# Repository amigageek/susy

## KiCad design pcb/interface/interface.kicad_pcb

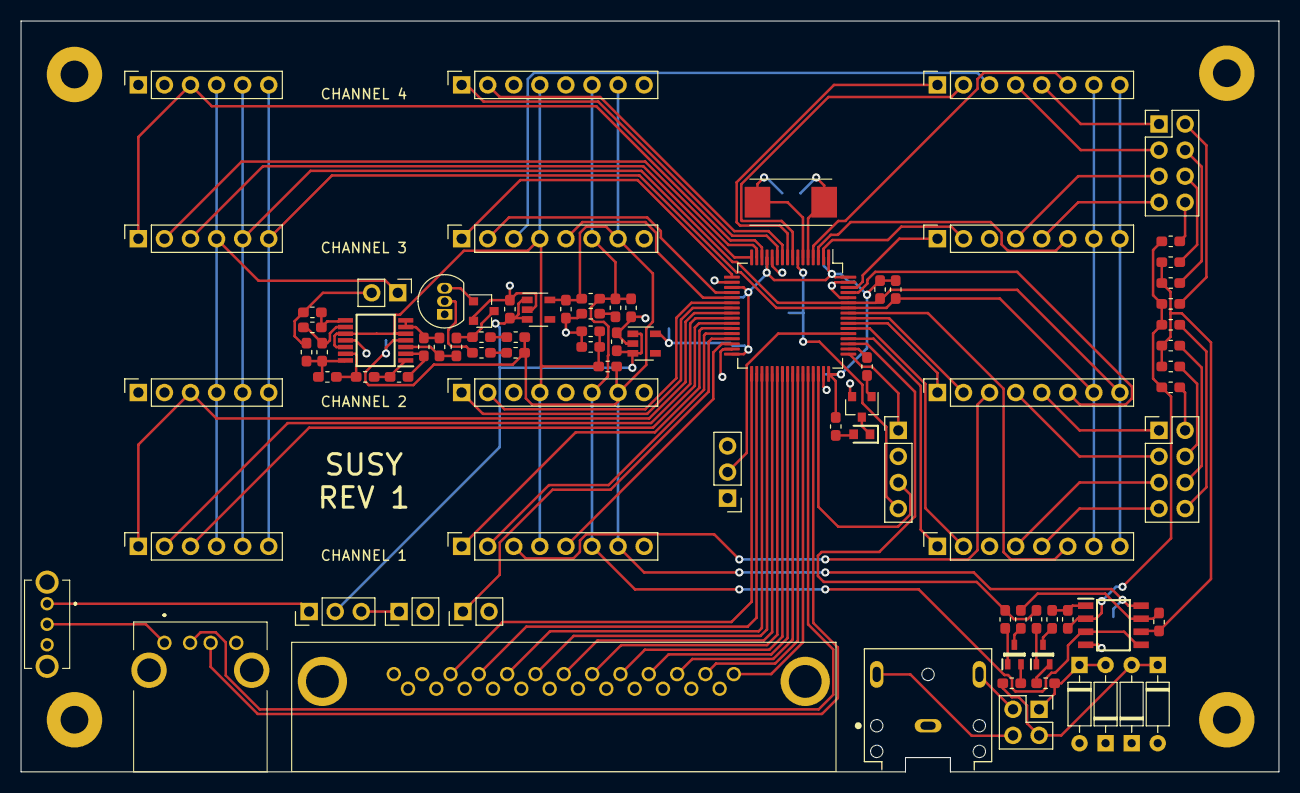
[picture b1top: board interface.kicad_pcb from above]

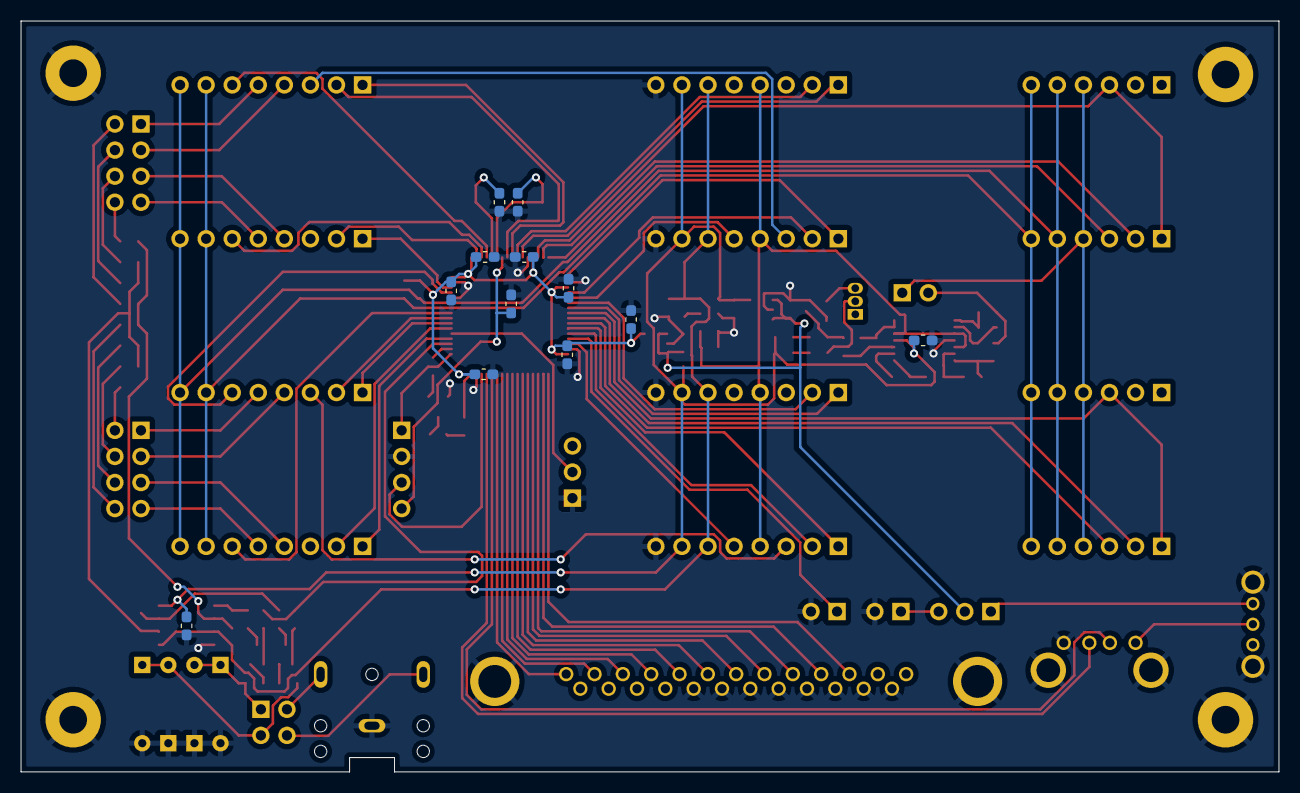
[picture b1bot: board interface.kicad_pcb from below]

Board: 2 copper layers, 122.6 x 73.2 mm, 101 parts (12 on the bottom side), 112 nets.

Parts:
C1, C2, C3, C4, C5, C6, C16, C19, C20: 100nF; C_0603_1608Metric_Pad1.05x0.95mm_HandSolder
C7: 10nF; C_0603_1608Metric_Pad1.05x0.95mm_HandSolder
C8, C10, C14, C15, C17, C18: 1uF; C_0603_1608Metric_Pad1.05x0.95mm_HandSolder
C9, C11: 4.7uF; C_0603_1608Metric_Pad1.05x0.95mm_HandSolder
C12, C13: 8pF; C_0603_1608Metric_Pad1.05x0.95mm_HandSolder
D1, D2, D3, D4: 1N4148; D_DO-35_SOD27_P7.62mm_Horizontal
H1, H2, H3, H4: MountingHole_Pad; MountingHole_2.7mm_M2.5_Pad
IC1: MCP6072-E_SN; SOIC127P600X175-8N
IC2: MCP6074-E_ST; SOP65P640X120-14N
J1, J2, J3, J4: Conn_01x06_Female; PinSocket_1x06_P2.54mm_Vertical
J5, J6, J7, J8, J9, J10, J11, J12: Conn_01x08_Female; PinSocket_1x08_P2.54mm_Vertical
J13: Conn_01x04_Male; PinHeader_1x04_P2.54mm_Vertical
J14: Parallel/USB; PinHeader_1x03_P2.54mm_Vertical
J15: D25S33E4PA00LF
J16: UJ2-AH-4-TH; UJ2AH4TH
J17: Spare; PinHeader_1x02_P2.54mm_Vertical
J18: Pwr Sel; PinHeader_1x03_P2.54mm_Vertical
J19: Pwr Ext; PinHeader_1x02_P2.54mm_Vertical
J20: SJ1-3523N; CUI_SJ1-3523N
J21: Conn_01x02_Male; PinHeader_1x02_P2.54mm_Vertical
J22: Conn_02x02_Top_Bottom; PinHeader_2x02_P2.54mm_Vertical
J23, J24: Conn_02x04_Top_Bottom; PinHeader_2x04_P2.54mm_Vertical
LED1: SML-D12U1WT86; LEDC1608X65N
Q1, Q4: MMBT3904; SOT-23
Q2, Q3: NX3008NBKW,115; SOT65P210X110-3N
R1, R2: 10k; R_0603_1608Metric_Pad1.05x0.95mm_HandSolder
R3: 47; R_0603_1608Metric_Pad1.05x0.95mm_HandSolder
R4: 33K; R_0603_1608Metric_Pad1.05x0.95mm_HandSolder
R5, R6, R7, R8, R9, R10, R12, R14, R15, R16, R17, R19, R20, R21, R22, R30, R32: 100k; R_0603_1608Metric_Pad1.05x0.95mm_HandSolder
R11, R13: 1k; R_0603_1608Metric_Pad1.05x0.95mm_HandSolder
R18, R23: 300k; R_0603_1608Metric_Pad1.05x0.95mm_HandSolder
R24, R25, R26, R27, R29, R33, R34: 1; R_0603_1608Metric_Pad1.05x0.95mm_HandSolder
R28, R31: 2k; R_0603_1608Metric_Pad1.05x0.95mm_HandSolder
R35, R36: 0; R_0603_1608Metric_Pad1.05x0.95mm_HandSolder
S1: OS102011MA1QN1C
U1: STM32F070RBTx; LQFP-64_10x10mm_P0.5mm
U2, U3: MIC5365-3.3YD5; SOT-23-5
U4: LM385BZ-1.2; TO-92_Inline
Y1: NX8045GB-8.000M-STD-CSJ-1; NX8045GB8000MSTDCSJ1

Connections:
/Line Driver (L)/LINE_OUT: D1.2, D2.1, J22.1, R11.1
/Line Driver (R)/LINE_OUT: D3.2, D4.1, J22.2, R13.1
/Mixer (L)/IN1: J24.8, R14.2
/Mixer (L)/IN2: J24.2, R15.2
/Mixer (L)/IN3: J23.8, R16.2
/Mixer (L)/IN4: J23.2, R17.2
/Mixer (L)/OP-: IC1.2, R14.1, R15.1, R16.1, R17.1, R18.2
/Mixer (R)/IN1: J24.6, R19.2
/Mixer (R)/IN2: J24.4, R20.2
/Mixer (R)/IN3: J23.6, R21.2
/Mixer (R)/IN4: J23.4, R22.2
/Mixer (R)/OP-: IC1.6, R19.1, R20.1, R21.1, R22.1, R23.2
/Noise/OUT: J21.2, R35.1, R36.1
/Regulator (VCC)/VIN: C8.1, C10.1, J18.2, U2.1, U2.3, U3.1, U3.3
FSEL1A: J9.2, U1.54
FSEL1B: J9.1, U1.52
FSEL2A: J10.2, U1.56
FSEL2B: J10.1, U1.55
FSEL3A: J11.2, U1.2
FSEL3B: J11.1, U1.62
FSEL4A: J12.2, U1.8
FSEL4B: J12.1, U1.9
GATE1: J9.6, U1.57
GATE2: J10.6, U1.61
GATE3: J11.6, U1.3
GATE4: J12.6, U1.4
GND: C1.2, C2.1, C3.1, C4.1, C5.1, C6.1, C7.1, C8.2, C9.2, C10.2, C11.2, C12.1, C13.1, C14.2, C15.2, C16.2, C20.2, D1.1, D2.2, D3.1, D4.2, H1.1, H2.1, H3.1, H4.1, IC1.4, IC2.11, J5.8, J6.8, J7.8, J8.8, J13.2, J14.1, J15.2, J15.4, J15.6, J15.8, J15.10, J15.12, J15.14, J15.16, J15.MH1, J15.MH2, J16.4, J16.MH1, J16.MH2, J17.2, J19.2, J20.1, Q1.2, Q4.2, R6.2, R9.2, S1.MH1, S1.MH2, U1.12, U1.18, U1.31, U1.47, U1.60, U1.63, U2.2, U3.2
LEFT: C17.2, IC1.1, R18.1
LEFT1: J9.5, J24.7
LEFT2: J10.5, J24.1
LEFT3: J11.5, J23.7
LEFT4: J12.5, J23.1
LINEL: J20.2, J22.3
LINER: J20.3, J22.4
LINE_EN: R10.1, R12.1, U1.51
NOISE: J1.4, J2.4, J3.4, J4.4, J21.1
unnamed: C1.1, J13.4, U1.7
unnamed: C12.2, U1.6, Y1.2
unnamed: C13.2, U1.5, Y1.1
unnamed: C17.1, Q2.3
unnamed: C18.1, Q3.3
unnamed: C19.1, IC2.3, R29.1
unnamed: C19.2, Q4.3, R27.2
unnamed: IC2.1, R30.1, R31.2
unnamed: IC2.2, R28.2, R30.2
unnamed: IC2.8, R33.2, R36.2
unnamed: IC2.9, R33.1, R34.2
unnamed: IC2.13, R31.1, R32.2
unnamed: IC2.14, R32.1, R34.1, R35.2
unnamed: J5.3, J10.3
unnamed: J7.3, J12.3
unnamed: J13.1, U1.49
unnamed: J13.3, U1.46
unnamed: J14.2, U1.53
unnamed: J16.1, S1.2
unnamed: J17.1, U1.29
unnamed: J18.3, J19.1
unnamed: LED1.1, Q1.3
unnamed: LED1.2, R3.2
unnamed: Q1.1, R4.2
unnamed: Q2.1, R10.2
unnamed: Q2.2, R11.2
unnamed: Q3.1, R12.2
unnamed: Q3.2, R13.2
unnamed: Q4.1, U4.3
unnamed: R4.1, U1.50
unnamed: R8.2, R9.1
unnamed: R24.2, R25.1
unnamed: R25.2, U4.2
unnamed: R26.2, R27.1
OSEL1A: J5.2, U1.28
OSEL1B: J5.1, U1.27
OSEL2A: J6.2, U1.22
OSEL2B: J6.1, U1.23
OSEL3A: J7.2, U1.20
OSEL3B: J7.1, U1.17
OSEL4A: J8.2, U1.10
OSEL4B: J8.1, U1.11
PACK: J15.7, U1.34
PBUSY: J15.5, U1.33
PDATA0: J15.23, U1.42
PDATA1: J15.21, U1.41
PDATA2: J15.19, U1.40
PDATA3: J15.17, U1.39
PDATA4: J15.15, U1.38
PDATA5: J15.13, U1.37
PDATA6: J15.11, U1.36
PDATA7: J15.9, U1.35
PSTROBE: J15.25, U1.43
RIGHT: C18.2, IC1.7, R23.1
RIGHT1: J9.4, J24.5
RIGHT2: J10.4, J24.3
RIGHT3: J11.4, J23.5
RIGHT4: J12.4, J23.3
RMSEL1: J5.5, U1.30
RMSEL2: J7.5, U1.21
SCL: J1.6, J2.6, J3.6, J4.6, J9.7, J10.7, J11.7, J12.7, R1.2, U1.58
SDA: J1.5, J2.5, J3.5, J4.5, J9.8, J10.8, J11.8, J12.8, R2.2, U1.59
SYNC_DIS1: J1.2, U1.25
SYNC_DIS2: J3.2, U1.15
SYNC_OUT1: J1.3, U1.26
SYNC_OUT2: J1.1, J2.3, U1.24
SYNC_OUT3: J3.3, U1.16
SYNC_OUT4: J3.1, J4.3, U1.14
UDATA+: J16.3, U1.45
UDATA-: J16.2, U1.44
VBUS: J18.1, S1.1
VCC: C9.1, C16.1, C20.1, IC1.8, IC2.4, J5.7, J6.7, J7.7, J8.7, R5.1, R7.1, R24.1, R26.1, U2.5
VDD: C2.2, C3.2, C4.2, C5.2, C6.2, C7.2, C11.1, R1.1, R2.1, R3.1, U1.1, U1.13, U1.19, U1.32, U1.48, U1.64, U3.5
VGND_REF: C15.1, IC1.3, IC1.5, J5.6, J6.6, J7.6, J8.6, R7.2, R8.1
VHALF: IC2.6, IC2.7, R28.1, R29.2
VHALF_REF: C14.1, IC2.5, IC2.10, IC2.12, J5.4, J6.4, J7.4, J8.4, R5.2, R6.1

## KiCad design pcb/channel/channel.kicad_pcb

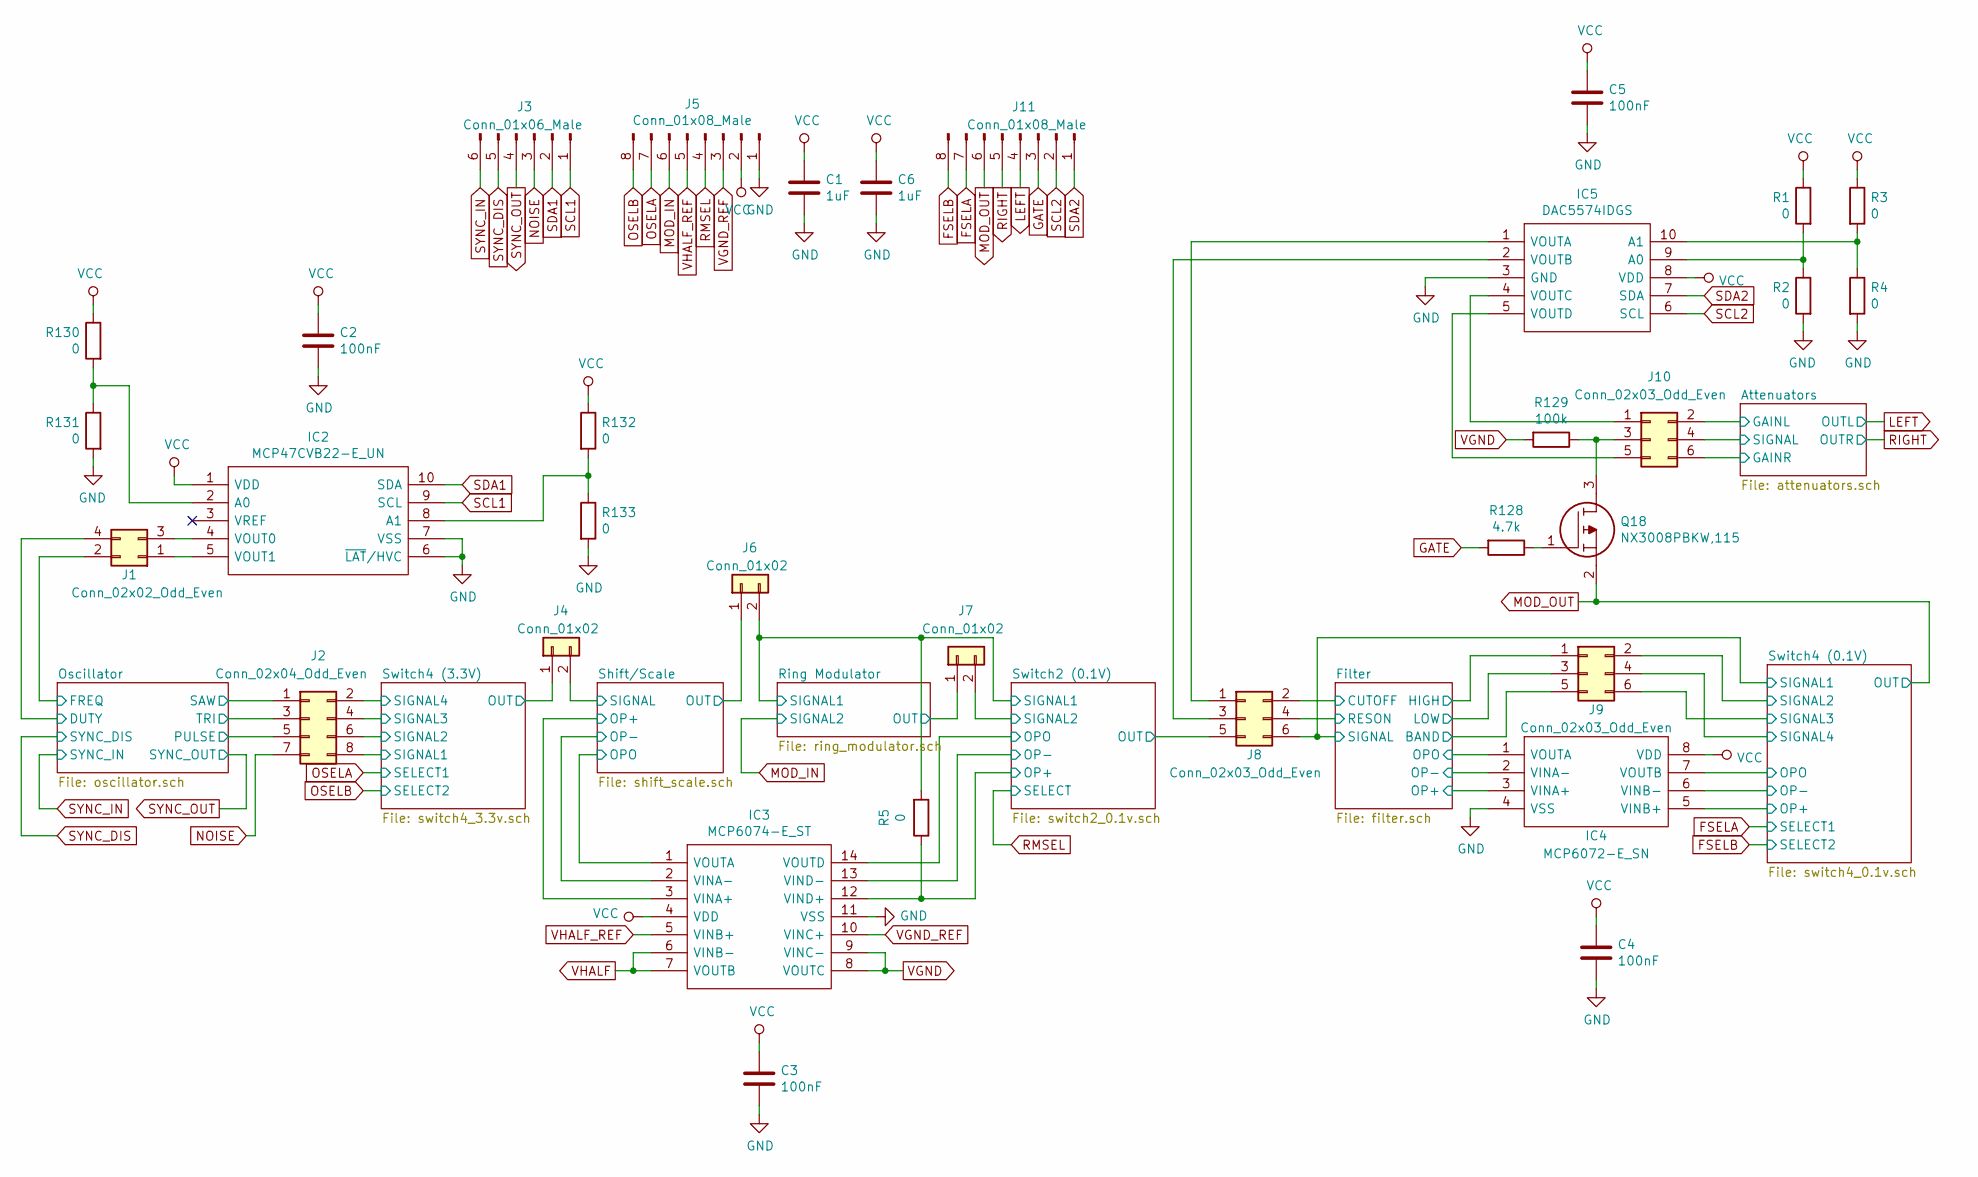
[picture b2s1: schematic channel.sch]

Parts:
C1, C6: 1uF; C_0603_1608Metric_Pad1.08x0.95mm_HandSolder
C2, C3, C4, C5: 100nF; C_0603_1608Metric_Pad1.08x0.95mm_HandSolder
IC2: MCP47CVB22-E_UN; SOP50P490X110-10N; Manufacturer_Part_Number MCP47CVB22-E/UN; Mouser Part Number 579-MCP47CVB22-E/UN
IC3: MCP6074-E_ST; SOP65P640X120-14N; Manufacturer_Part_Number MCP6074-E/ST; Mouser Part Number 579-MCP6074-E/ST
IC4: MCP6072-E_SN; SOIC127P600X175-8N; Manufacturer_Part_Number MCP6072-E/SN; Mouser Part Number 579-MCP6072-E/SN
IC5: DAC5574IDGS; SOP50P490X110-10N; Manufacturer_Part_Number DAC5574IDGS; Mouser Part Number 595-DAC5574IDGS
J1: Conn_02x02_Odd_Even; PinHeader_2x02_P2.54mm_Vertical
J2: Conn_02x04_Odd_Even; PinHeader_2x04_P2.54mm_Vertical
J3: Conn_01x06_Male; PinHeader_1x06_P2.54mm_Horizontal
J4, J6, J7: Conn_01x02; PinHeader_1x02_P2.54mm_Vertical
J5, J11: Conn_01x08_Male; PinHeader_1x08_P2.54mm_Horizontal
J8, J9, J10: Conn_02x03_Odd_Even; PinHeader_2x03_P2.54mm_Vertical
Q18: NX3008PBKW,115; SOT65P210X110-3N; Manufacturer_Part_Number NX3008PBKW,115; Mouser Part Number 771-NX3008PBKW,115
R1, R2, R3, R4, R5, R130, R131, R132, R133: 0; R_0603_1608Metric_Pad1.05x0.95mm_HandSolder
R128: 4.7k; R_0603_1608Metric_Pad1.05x0.95mm_HandSolder
R129: 100k; R_0603_1608Metric_Pad1.05x0.95mm_HandSolder

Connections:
/Attenuators/GAINL: J10.2; also elsewhere on the board
/Attenuators/GAINR: J10.6; also elsewhere on the board
/Attenuators/SIGNAL: J10.4; also elsewhere on the board
/Filter/BAND: J9.5; also elsewhere on the board
/Filter/CUTOFF: J8.2; also elsewhere on the board
/Filter/HIGH: J9.1; also elsewhere on the board
/Filter/LOW: J9.3; also elsewhere on the board
/Filter/OP+: IC4.3 (VINA+); also elsewhere on the board
/Filter/OP-: IC4.2 (VINA-); also elsewhere on the board
/Filter/OPO: IC4.1 (VOUTA); also elsewhere on the board
/Filter/RESON: J8.4; also elsewhere on the board
/Filter/SIGNAL: J8.6; also elsewhere on the board
/Oscillator/DUTY: J1.4; also elsewhere on the board
/Oscillator/FREQ: J1.2; also elsewhere on the board
/Oscillator/PULSE: J2.5; also elsewhere on the board
/Oscillator/SAW: J2.1; also elsewhere on the board
/Oscillator/TRI: J2.3; also elsewhere on the board
/Ring Modulator/OUT: J7.1; also elsewhere on the board
/Ring Modulator/SIGNAL1: J6.2, R5.2; also elsewhere on the board
/Shift/Scale/OP+: IC3.3 (VINA+); also elsewhere on the board
/Shift/Scale/OP-: IC3.2 (VINA-); also elsewhere on the board
/Shift/Scale/OPO: IC3.1 (VOUTA), J6.1; also elsewhere on the board
/Shift/Scale/SIGNAL: J4.2; also elsewhere on the board
/Switch2 (0.1V)/OP+: IC3.12 (VIND+), R5.1; also elsewhere on the board
/Switch2 (0.1V)/OP-: IC3.13 (VIND-), IC3.14 (VOUTD), J8.5
/Switch2 (0.1V)/SIGNAL2: J7.2; also elsewhere on the board
/Switch4 (0.1V)/OP+: IC4.5 (VINB+); also elsewhere on the board
/Switch4 (0.1V)/SIGNAL2: J9.2; also elsewhere on the board
/Switch4 (0.1V)/SIGNAL3: J9.6; also elsewhere on the board
/Switch4 (0.1V)/SIGNAL4: J9.4; also elsewhere on the board
/Switch4 (3.3V)/OUT: J4.1; also elsewhere on the board
/Switch4 (3.3V)/SIGNAL1: J2.8; also elsewhere on the board
/Switch4 (3.3V)/SIGNAL2: J2.6; also elsewhere on the board
/Switch4 (3.3V)/SIGNAL3: J2.4; also elsewhere on the board
/Switch4 (3.3V)/SIGNAL4: J2.2; also elsewhere on the board
FSELA: J11.7; also elsewhere on the board
FSELB: J11.8; also elsewhere on the board
GATE: J11.3, R128.2
GND: C1.2, C2.2, C3.2, C4.2, C5.2, C6.2, IC2.6 (~LAT~/HVC), IC2.7 (VSS), IC3.11 (VSS), IC4.4 (VSS), IC5.3 (GND), J5.1, R2.2, R4.2, R131.2, R133.2; also elsewhere on the board
LEFT: J11.4; also elsewhere on the board
MOD_IN: J5.6; also elsewhere on the board
MOD_OUT: IC4.6 (VINB-), IC4.7 (VOUTB), J11.6, Q18.2
NOISE: J2.7, J3.3
unnamed: IC2.2 (A0), R130.2, R131.1
unnamed: IC2.4 (VOUT0), J1.3
unnamed: IC2.5 (VOUT1), J1.1
unnamed: IC2.8 (A1), R132.2, R133.1
unnamed: IC5.1 (VOUTA), J8.1
unnamed: IC5.2 (VOUTB), J8.3
unnamed: IC5.4 (VOUTC), J10.1
unnamed: IC5.5 (VOUTD), J10.5
unnamed: IC5.9 (A0), R1.2, R2.1
unnamed: IC5.10 (A1), R3.2, R4.1
unnamed: J10.3, Q18.3, R129.1
unnamed: Q18.1, R128.1
OSELA: J5.7; also elsewhere on the board
OSELB: J5.8; also elsewhere on the board
RIGHT: J11.5; also elsewhere on the board
RMSEL: J5.4; also elsewhere on the board
SCL1: IC2.9 (SCL), J3.1
SCL2: IC5.6 (SCL), J11.2
SDA1: IC2.10 (SDA), J3.2
SDA2: IC5.7 (SDA), J11.1
SYNC_DIS: J3.5; also elsewhere on the board
SYNC_IN: J3.6; also elsewhere on the board
SYNC_OUT: J3.4; also elsewhere on the board
VCC: C1.1, C2.1, C3.1, C4.1, C5.1, C6.1, IC2.1 (VDD), IC3.4 (VDD), IC4.8 (VDD), IC5.8 (VDD), J5.2, R1.1, R3.1, R130.1, R132.1; also elsewhere on the board
VGND: IC3.8 (VOUTC), IC3.9 (VINC-), R129.2; also elsewhere on the board
VGND_REF: IC3.10 (VINC+), J5.3
VHALF: IC3.6 (VINB-), IC3.7 (VOUTB); also elsewhere on the board
VHALF_REF: IC3.5 (VINB+), J5.5

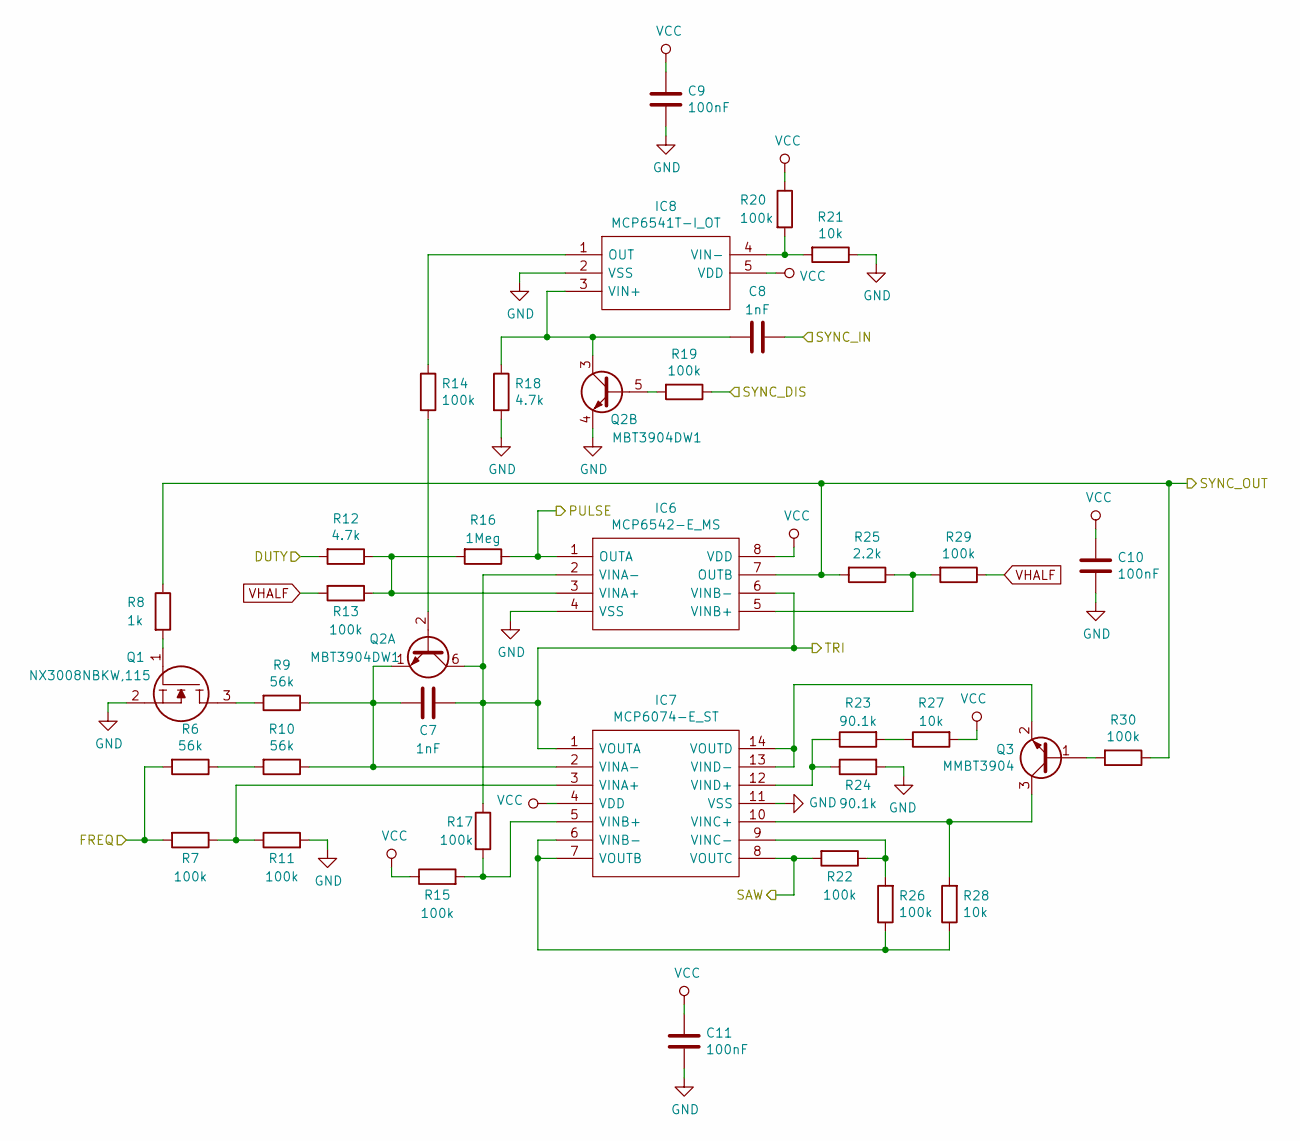
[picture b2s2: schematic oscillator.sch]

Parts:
C7, C8: 1nF; C_0603_1608Metric_Pad1.08x0.95mm_HandSolder
C9, C10, C11: 100nF; C_0603_1608Metric_Pad1.08x0.95mm_HandSolder
IC6: MCP6542-E_MS; SOP65P490X110-8N; Manufacturer_Part_Number MCP6542-E/MS; Mouser Part Number 579-MCP6542-E/MS
IC7: MCP6074-E_ST; SOP65P640X120-14N; Manufacturer_Part_Number MCP6074-E/ST; Mouser Part Number 579-MCP6074-E/ST
IC8: MCP6541T-I_OT; SOT95P270X145-5N; Manufacturer_Part_Number MCP6541T-I/OT; Mouser Part Number 579-MCP6541T-I/OT
Q1: NX3008NBKW,115; SOT65P210X110-3N; Manufacturer_Part_Number NX3008NBKW,115; Mouser Part Number 771-NX3008NBKW,115
Q2: MBT3904DW1; SOT-363_SC-70-6
Q3: MMBT3904; SOT-23
R6, R9, R10: 56k; R_0603_1608Metric_Pad1.05x0.95mm_HandSolder
R7, R11, R13, R14, R15, R17, R19, R20, R22, R26, R29, R30: 100k; R_0603_1608Metric_Pad1.05x0.95mm_HandSolder
R8: 1k; R_0603_1608Metric_Pad1.05x0.95mm_HandSolder
R12, R18: 4.7k; R_0603_1608Metric_Pad1.05x0.95mm_HandSolder
R16: 1Meg; R_0603_1608Metric_Pad1.05x0.95mm_HandSolder
R21, R27, R28: 10k; R_0603_1608Metric_Pad1.05x0.95mm_HandSolder
R23, R24: 90.1k; R_0603_1608Metric_Pad1.05x0.95mm_HandSolder
R25: 2.2k; R_0603_1608Metric_Pad1.05x0.95mm_HandSolder

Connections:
/Oscillator/DUTY: R12.2; also elsewhere on the board
/Oscillator/FREQ: R6.2, R7.2; also elsewhere on the board
/Oscillator/PULSE: IC6.1 (OUTA), R16.1; also elsewhere on the board
/Oscillator/SAW: IC7.8 (VOUTC), R22.2; also elsewhere on the board
/Oscillator/TRI: C7.1, IC6.2 (VINA-), IC6.6 (VINB-), IC7.1 (VOUTA), Q2.6 (C1), R17.1; also elsewhere on the board
GND: C9.2, C10.2, C11.2, IC6.4 (VSS), IC7.11 (VSS), IC8.2 (VSS), Q1.2, Q2.4 (E2), R11.2, R18.2, R21.1, R24.2; also elsewhere on the board
unnamed: C7.2, IC7.2 (VINA-), Q2.1 (E1), R9.1, R10.1
unnamed: C8.2, IC8.3 (VIN+), Q2.3 (C2), R18.1
unnamed: IC6.3 (VINA+), R12.1, R13.1, R16.2
unnamed: IC6.5 (VINB+), R25.1, R29.2
unnamed: IC7.3 (VINA+), R7.1, R11.1
unnamed: IC7.5 (VINB+), R15.2, R17.2
unnamed: IC7.6 (VINB-), IC7.7 (VOUTB), R26.1, R28.1
unnamed: IC7.9 (VINC-), R22.1, R26.2
unnamed: IC7.10 (VINC+), Q3.3 (C), R28.2
unnamed: IC7.12 (VIND+), R23.1, R24.1
unnamed: IC7.13 (VIND-), IC7.14 (VOUTD), Q3.2 (E)
unnamed: IC8.1 (OUT), R14.1
unnamed: IC8.4 (VIN-), R20.2, R21.2
unnamed: Q1.1, R8.2
unnamed: Q1.3, R9.2
unnamed: Q2.2 (B1), R14.2
unnamed: Q2.5 (B2), R19.2
unnamed: Q3.1 (B), R30.2
unnamed: R6.1, R10.2
unnamed: R23.2, R27.1
SYNC_DIS: R19.1; also elsewhere on the board
SYNC_IN: C8.1; also elsewhere on the board
SYNC_OUT: IC6.7 (OUTB), R8.1, R25.2, R30.1; also elsewhere on the board
VCC: C9.1, C10.1, C11.1, IC6.8 (VDD), IC7.4 (VDD), IC8.5 (VDD), R15.1, R20.1, R27.2; also elsewhere on the board
VHALF: R13.2, R29.1; also elsewhere on the board

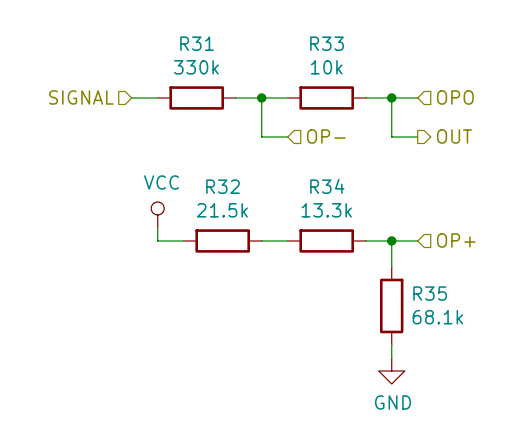
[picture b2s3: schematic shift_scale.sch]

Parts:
R31: 330k; R_0603_1608Metric_Pad1.05x0.95mm_HandSolder
R32: 21.5k; R_0603_1608Metric_Pad1.05x0.95mm_HandSolder
R33: 10k; R_0603_1608Metric_Pad1.05x0.95mm_HandSolder
R34: 13.3k; R_0603_1608Metric_Pad1.05x0.95mm_HandSolder
R35: 68.1k; R_0603_1608Metric_Pad1.05x0.95mm_HandSolder

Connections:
/Shift/Scale/OP+: R34.1, R35.2; also elsewhere on the board
/Shift/Scale/OP-: R31.1, R33.2; also elsewhere on the board
/Shift/Scale/OPO: R33.1; also elsewhere on the board
/Shift/Scale/SIGNAL: R31.2; also elsewhere on the board
GND: R35.1; also elsewhere on the board
unnamed: R32.1, R34.2
VCC: R32.2; also elsewhere on the board

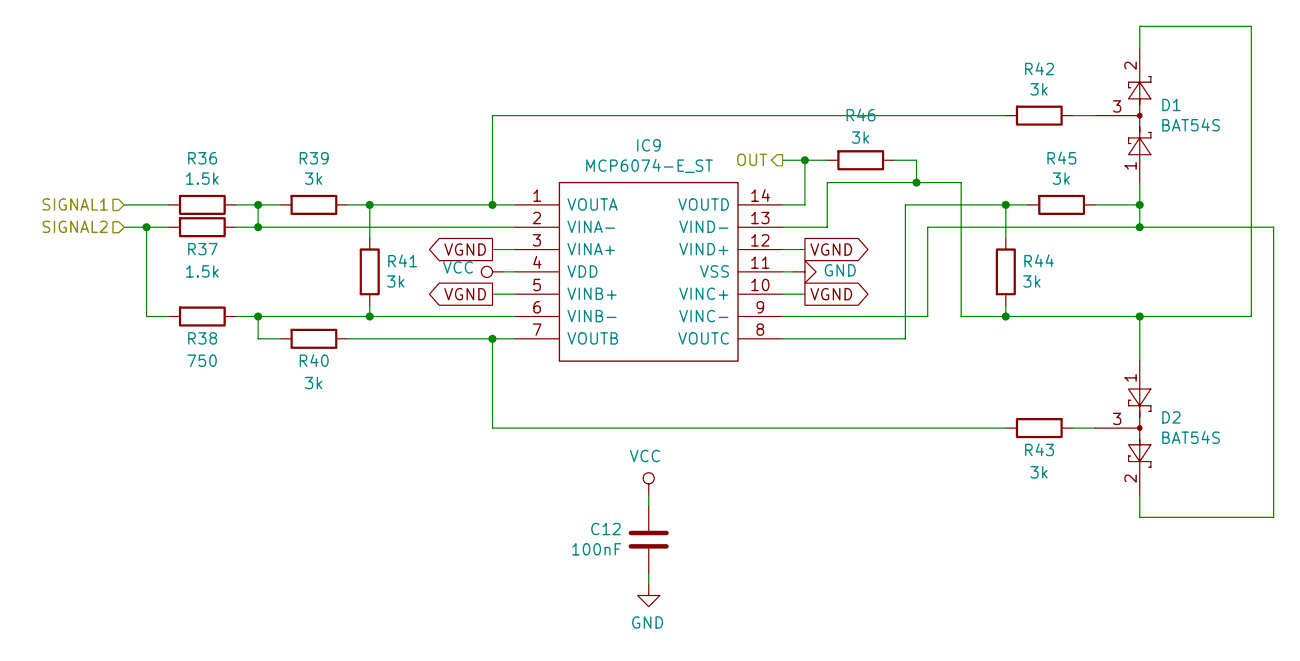
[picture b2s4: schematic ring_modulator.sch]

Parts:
C12: 100nF; C_0603_1608Metric_Pad1.08x0.95mm_HandSolder
D1, D2: BAT54S; SOT-23
IC9: MCP6074-E_ST; SOP65P640X120-14N; Manufacturer_Part_Number MCP6074-E/ST; Mouser Part Number 579-MCP6074-E/ST
R36, R37: 1.5k; R_0603_1608Metric_Pad1.05x0.95mm_HandSolder
R38: 750; R_0603_1608Metric_Pad1.05x0.95mm_HandSolder
R39, R40, R41, R42, R43, R44, R45, R46: 3k; R_0603_1608Metric_Pad1.05x0.95mm_HandSolder

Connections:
/Ring Modulator/OUT: IC9.14 (VOUTD), R46.2; also elsewhere on the board
/Ring Modulator/SIGNAL1: R36.2; also elsewhere on the board
GND: C12.2, IC9.11 (VSS); also elsewhere on the board
MOD_IN: R37.2, R38.2; also elsewhere on the board
unnamed: D1.1, D2.2, IC9.9 (VINC-), R45.1
unnamed: D1.2, D2.1, IC9.13 (VIND-), R44.2, R46.1
unnamed: D1.3, R42.1
unnamed: D2.3, R43.2
unnamed: IC9.1 (VOUTA), R39.1, R41.1, R42.2
unnamed: IC9.2 (VINA-), R36.1, R37.1, R39.2
unnamed: IC9.6 (VINB-), R38.1, R40.2, R41.2
unnamed: IC9.7 (VOUTB), R40.1, R43.1
unnamed: IC9.8 (VOUTC), R44.1, R45.2
VCC: C12.1, IC9.4 (VDD); also elsewhere on the board
VGND: IC9.3 (VINA+), IC9.5 (VINB+), IC9.10 (VINC+), IC9.12 (VIND+); also elsewhere on the board

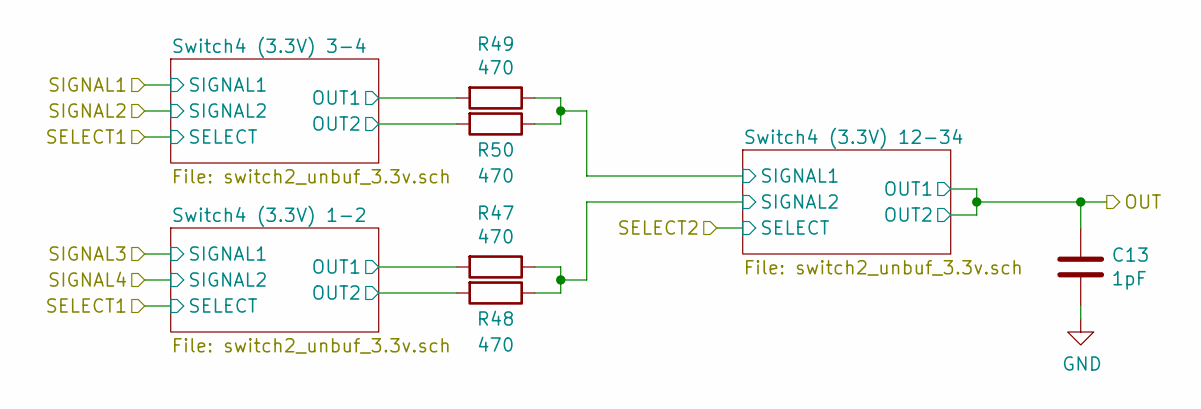
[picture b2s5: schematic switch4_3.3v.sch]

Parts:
C13: 1pF; C_0603_1608Metric_Pad1.08x0.95mm_HandSolder
R47, R48, R49, R50: 470; R_0603_1608Metric_Pad1.05x0.95mm_HandSolder

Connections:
/Switch4 (3.3V)/OUT: C13.1; also elsewhere on the board
/Switch4 (3.3V)/Switch4 (3.3V) 1-2/OUT1: R47.2; also elsewhere on the board
/Switch4 (3.3V)/Switch4 (3.3V) 1-2/OUT2: R48.2; also elsewhere on the board
/Switch4 (3.3V)/Switch4 (3.3V) 3-4/OUT1: R49.2; also elsewhere on the board
/Switch4 (3.3V)/Switch4 (3.3V) 3-4/OUT2: R50.2; also elsewhere on the board
/Switch4 (3.3V)/Switch4 (3.3V) 12-34/SIGNAL1: R49.1, R50.1; also elsewhere on the board
/Switch4 (3.3V)/Switch4 (3.3V) 12-34/SIGNAL2: R47.1, R48.1; also elsewhere on the board
GND: C13.2; also elsewhere on the board

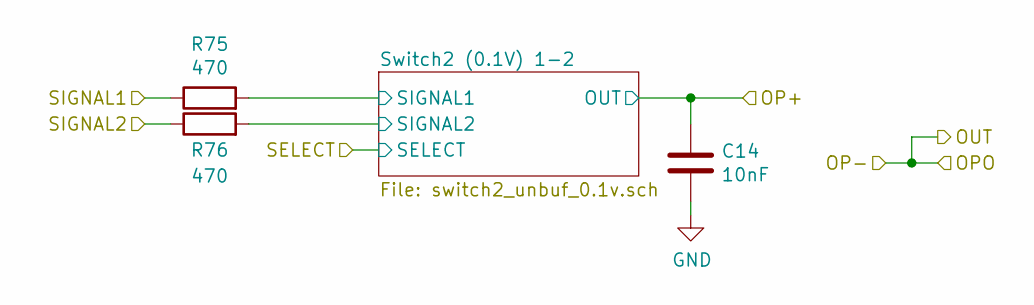
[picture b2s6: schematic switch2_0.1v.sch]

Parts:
C14: 10nF; C_0603_1608Metric_Pad1.08x0.95mm_HandSolder
R75, R76: 470; R_0603_1608Metric_Pad1.05x0.95mm_HandSolder

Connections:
/Ring Modulator/SIGNAL1: R75.1; also elsewhere on the board
/Switch2 (0.1V)/OP+: C14.1; also elsewhere on the board
/Switch2 (0.1V)/SIGNAL2: R76.1; also elsewhere on the board
/Switch2 (0.1V)/Switch2 (0.1V) 1-2/SIGNAL1: R75.2; also elsewhere on the board
/Switch2 (0.1V)/Switch2 (0.1V) 1-2/SIGNAL2: R76.2; also elsewhere on the board
GND: C14.2; also elsewhere on the board

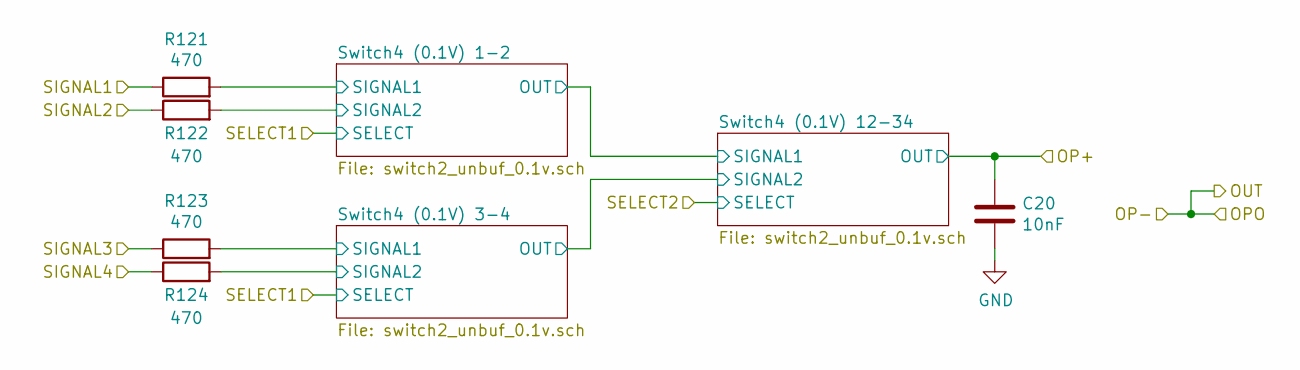
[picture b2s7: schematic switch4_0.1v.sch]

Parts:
C20: 10nF; C_0603_1608Metric_Pad1.08x0.95mm_HandSolder
R121, R122, R123, R124: 470; R_0603_1608Metric_Pad1.05x0.95mm_HandSolder

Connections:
/Filter/SIGNAL: R121.1; also elsewhere on the board
/Switch4 (0.1V)/OP+: C20.1; also elsewhere on the board
/Switch4 (0.1V)/SIGNAL2: R122.1; also elsewhere on the board
/Switch4 (0.1V)/SIGNAL3: R123.1; also elsewhere on the board
/Switch4 (0.1V)/SIGNAL4: R124.1; also elsewhere on the board
/Switch4 (0.1V)/Switch4 (0.1V) 1-2/SIGNAL1: R121.2; also elsewhere on the board
/Switch4 (0.1V)/Switch4 (0.1V) 1-2/SIGNAL2: R122.2; also elsewhere on the board
/Switch4 (0.1V)/Switch4 (0.1V) 3-4/SIGNAL1: R123.2; also elsewhere on the board
/Switch4 (0.1V)/Switch4 (0.1V) 3-4/SIGNAL2: R124.2; also elsewhere on the board
GND: C20.2; also elsewhere on the board

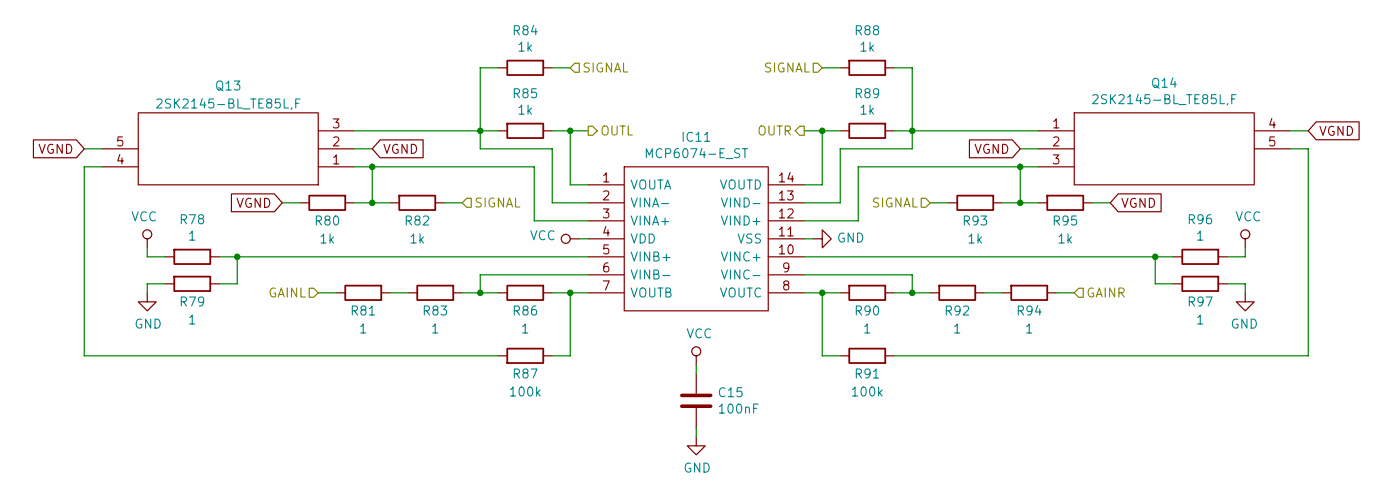
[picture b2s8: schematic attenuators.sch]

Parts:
C15: 100nF; C_0603_1608Metric_Pad1.08x0.95mm_HandSolder
IC11: MCP6074-E_ST; SOP65P640X120-14N; Manufacturer_Part_Number MCP6074-E/ST; Mouser Part Number 579-MCP6074-E/ST
Q13, Q14: 2SK2145-BL_TE85L,F; SOT95P275X130-5N; Manufacturer_Part_Number 2SK2145-BL(TE85L,F; Mouser Part Number 757-2SK2145BLTE85LF
R78, R79, R81, R83, R86, R90, R92, R94, R96, R97: 1; R_0603_1608Metric_Pad1.05x0.95mm_HandSolder
R80, R82, R84, R85, R88, R89, R93, R95: 1k; R_0603_1608Metric_Pad1.05x0.95mm_HandSolder
R87, R91: 100k; R_0603_1608Metric_Pad1.05x0.95mm_HandSolder

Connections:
/Attenuators/GAINL: R81.1; also elsewhere on the board
/Attenuators/GAINR: R94.1; also elsewhere on the board
/Attenuators/SIGNAL: R82.1, R84.2, R88.2, R93.1; also elsewhere on the board
GND: C15.2, IC11.11 (VSS), R79.2, R97.2; also elsewhere on the board
LEFT: IC11.1 (VOUTA), R85.1; also elsewhere on the board
unnamed: IC11.2 (VINA-), Q13.3, R84.1, R85.2
unnamed: IC11.3 (VINA+), Q13.1, R80.2, R82.2
unnamed: IC11.5 (VINB+), R78.1, R79.1
unnamed: IC11.6 (VINB-), R83.2, R86.1
unnamed: IC11.7 (VOUTB), R86.2, R87.1
unnamed: IC11.8 (VOUTC), R90.2, R91.1
unnamed: IC11.9 (VINC-), R90.1, R92.2
unnamed: IC11.10 (VINC+), R96.1, R97.1
unnamed: IC11.12 (VIND+), Q14.3, R93.2, R95.2
unnamed: IC11.13 (VIND-), Q14.1, R88.1, R89.2
unnamed: Q13.4, R87.2
unnamed: Q14.5, R91.2
unnamed: R81.2, R83.1
unnamed: R92.1, R94.2
RIGHT: IC11.14 (VOUTD), R89.1; also elsewhere on the board
VCC: C15.1, IC11.4 (VDD), R78.2, R96.2; also elsewhere on the board
VGND: Q13.2, Q13.5, Q14.2, Q14.4, R80.1, R95.1; also elsewhere on the board

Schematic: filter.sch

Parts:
C16, C17: 100nF; C_0603_1608Metric_Pad1.08x0.95mm_HandSolder
C18, C19: 500nF; C_0603_1608Metric_Pad1.08x0.95mm_HandSolder
IC12, IC13: MCP6074-E_ST; SOP65P640X120-14N; Manufacturer_Part_Number MCP6074-E/ST; Mouser Part Number 579-MCP6074-E/ST
R98, R99, R102: 100k; R_0603_1608Metric_Pad1.05x0.95mm_HandSolder
R100: 390; R_0603_1608Metric_Pad1.05x0.95mm_HandSolder
R101: 1k; R_0603_1608Metric_Pad1.05x0.95mm_HandSolder

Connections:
/Filter/BAND: C18.1, IC12.5 (VINB+), IC13.1 (VOUTA), R101.1; also elsewhere on the board
/Filter/HIGH: IC13.8 (VOUTC), IC13.12 (VIND+), R98.1; also elsewhere on the board
/Filter/JFET 1K-100 (1)/DRAIN: IC12.10 (VINC+), IC13.10 (VINC+), R100.2; also elsewhere on the board
/Filter/JFET 1K-100 (1)/OP1+: IC12.12 (VIND+); also elsewhere on the board
/Filter/JFET 1K-100 (1)/OP1-: IC12.13 (VIND-); also elsewhere on the board
/Filter/JFET 1K-100 (1)/OP1O: IC12.14 (VOUTD); also elsewhere on the board
/Filter/JFET 1K-100 (1)/OP2-: IC12.8 (VOUTC), IC12.9 (VINC-); also elsewhere on the board
/Filter/JFET 1K-100 (2)/OP2-: IC13.13 (VIND-), IC13.14 (VOUTD); also elsewhere on the board
/Filter/JFET 1K-100 (2)/SOURCE: C18.2, IC13.2 (VINA-); also elsewhere on the board
/Filter/JFET 1K-100 (3)/OP1+: IC12.3 (VINA+); also elsewhere on the board
/Filter/JFET 1K-100 (3)/OP1-: IC12.2 (VINA-); also elsewhere on the board
/Filter/JFET 1K-100 (3)/OP1O: IC12.1 (VOUTA); also elsewhere on the board
/Filter/JFET 1K-100 (3)/OP2-: IC12.6 (VINB-), IC12.7 (VOUTB); also elsewhere on the board
/Filter/JFET 1K-100 (3)/SOURCE: C19.1, IC13.6 (VINB-); also elsewhere on the board
/Filter/LOW: C19.2, IC13.7 (VOUTB), R102.1; also elsewhere on the board
/Filter/SIGNAL: R99.2; also elsewhere on the board
GND: C16.2, C17.2, IC12.11 (VSS), IC13.11 (VSS); also elsewhere on the board
unnamed: IC13.9 (VINC-), R98.2, R99.1, R102.2
unnamed: R100.1, R101.2
VCC: C16.1, C17.1, IC12.4 (VDD), IC13.4 (VDD); also elsewhere on the board
VGND: IC13.3 (VINA+), IC13.5 (VINB+); also elsewhere on the board
